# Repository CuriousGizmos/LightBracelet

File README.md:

LightBracelet
=============

A simple light bracelet design using a flexible circuit, smd components and a coin cell for power.

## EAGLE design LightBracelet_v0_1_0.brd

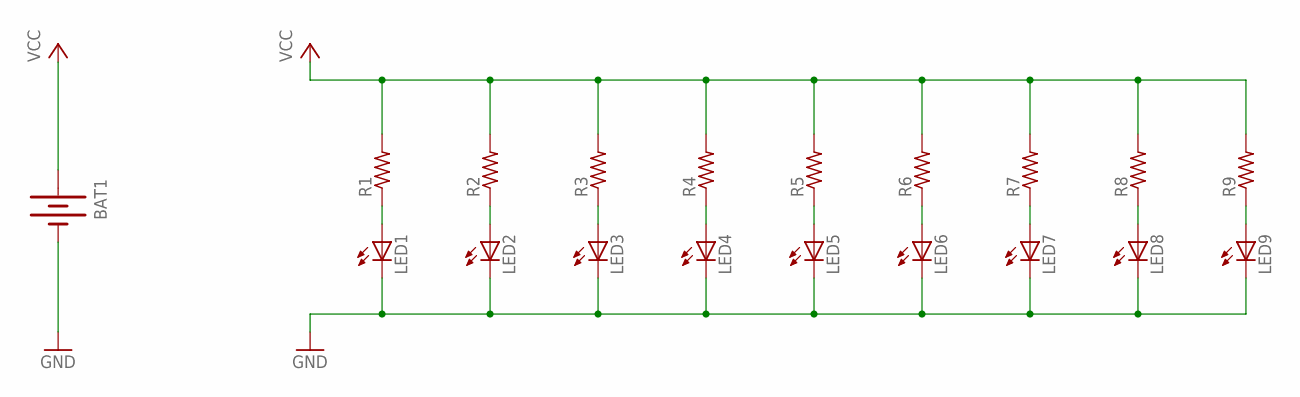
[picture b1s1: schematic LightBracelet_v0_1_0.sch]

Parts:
BAT1: BATTERY245MM; BATTCON_245MM
LED1, LED2, LED3, LED4, LED5, LED6, LED7, LED8, LED9: LEDCHIPLED_1206; CHIPLED_1206
R1, R2, R3, R4, R5, R6, R7, R8, R9: R-US_M0805; M0805

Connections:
GND: BAT1.2 (-), LED1.C, LED2.C, LED3.C, LED4.C, LED5.C, LED6.C, LED7.C, LED8.C, LED9.C
unnamed: LED1.A, R1.1
unnamed: LED2.A, R2.1
unnamed: LED3.A, R3.1
unnamed: LED4.A, R4.1
unnamed: LED5.A, R5.1
unnamed: LED6.A, R6.1
unnamed: LED7.A, R7.1
unnamed: LED8.A, R8.1
unnamed: LED9.A, R9.1
VCC: BAT1.1 (+), R1.2, R2.2, R3.2, R4.2, R5.2, R6.2, R7.2, R8.2, R9.2

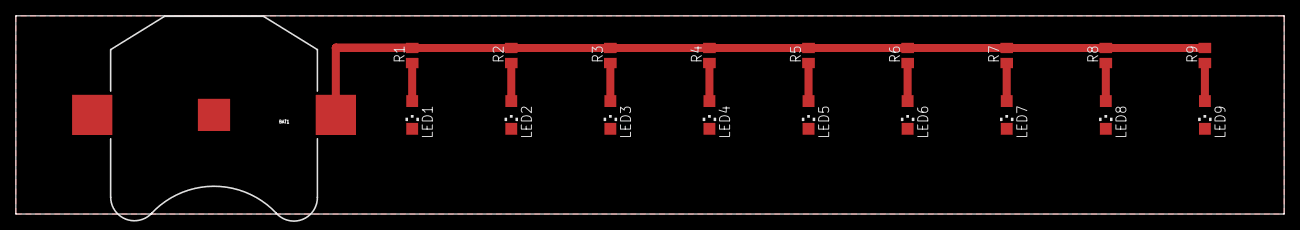
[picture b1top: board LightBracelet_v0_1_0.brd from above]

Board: 2 copper layers, 160.0 x 25.0 mm, 19 parts (0 on the bottom side), 11 nets.

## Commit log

2012-11-15 First commit w/ files
    Includes the design files plus pdfs of the PCB and Schematic.

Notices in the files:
parts and their libraries:
SparkFun: Licensing: CC v3.0 Share-Alike You are welcome to use this library for commercial purposes.
